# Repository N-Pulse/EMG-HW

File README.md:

# EMG-HW

This repository contains all the PCB designs for the EMG bracelet as part of a project semester at EPFL.

This work is licensed under a <a rel="license" href="https://creativecommons.org/licenses/by/4.0/">Creative Commons Attribution 4.0 International License</a>.

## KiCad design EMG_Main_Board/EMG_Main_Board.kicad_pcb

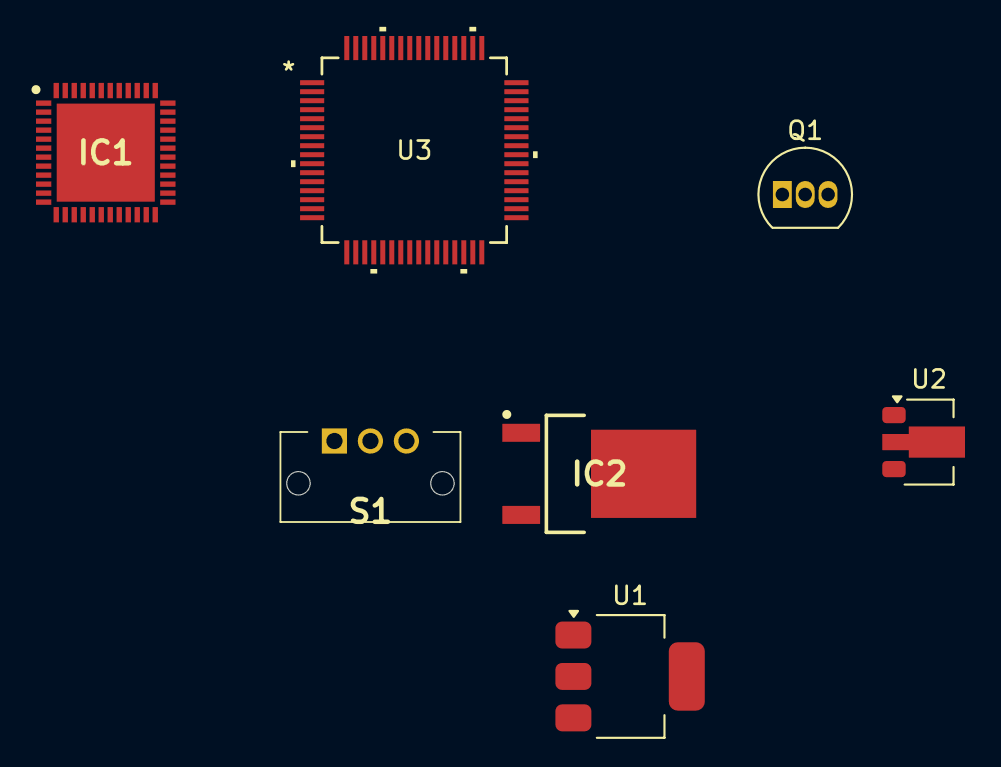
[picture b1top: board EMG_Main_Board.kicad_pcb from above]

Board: 2 copper layers, 7 parts (0 on the bottom side), 8 nets, no tracks yet.

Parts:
IC1: EFR32BG13P732F512GM48-D; QFN50P700X700X90-49N-D
IC2: LD1117DT18TR; TO228P972X240-3N
Q1: 2N3904; TO-92_Inline
S1: SC12P-AQR; SC12PAQR
U1: LD1117S33TR_SOT223; SOT-223-3_TabPin2
U2: NDP6802SF-33; SOT-89-3
U3: STM32G0B1RET6; LQFP_0B1RET6_STM

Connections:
GND: IC1.49 (VSS), IC2.1 (GND), Q1.1 (E), U1.1 (GND), U3.9 (VSS/VSSA)
unnamed: IC1.39 (VREGVDD), IC2.3 (VIN), S1.C1 (C1_NO), U3.8 (VDD/VDDA)
unnamed: Q1.3 (C), U2.2 (GND)
unnamed: S1.B1 (B1_COM), U1.2 (VO)
SPI_MISO: IC1.25 (PA0), U3.60 (PB6)
SPI_MOSI: IC1.26 (PA1), U3.61 (PB7)
SPI_NSS: IC1.28 (PA3), U3.63 (PB9)
SPI_SCK: IC1.27 (PA2), U3.62 (PB8)

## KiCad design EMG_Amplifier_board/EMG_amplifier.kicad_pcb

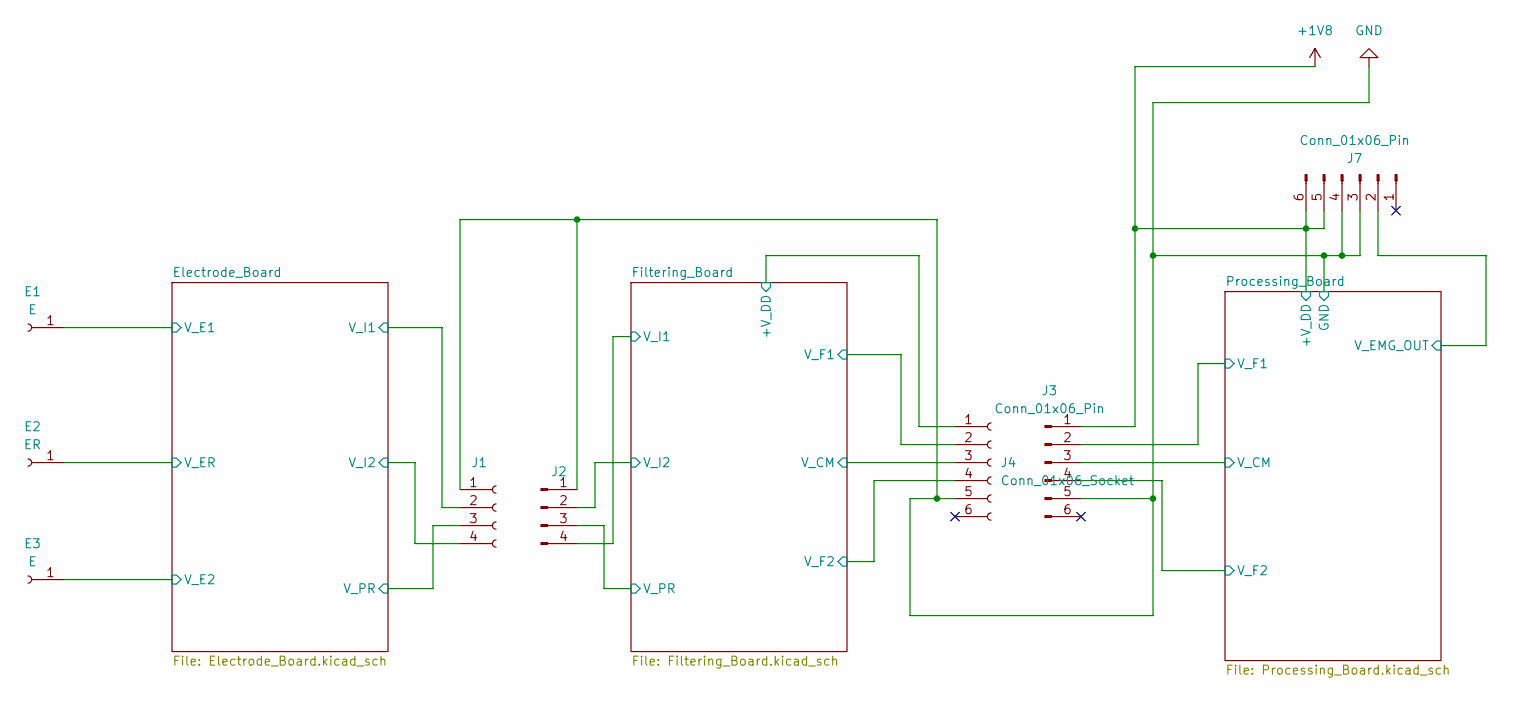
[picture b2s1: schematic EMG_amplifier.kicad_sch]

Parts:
E1, E3: E; Electrode_Shape
E2: ER; Electrode_Shape
J1: Conn_01x04_Socket; PinSocket_2x02_P2.54mm_Vertical
J2: Conn_01x04_Pin; PinHeader_2x02_P2.54mm_Vertical
J3, J7: Conn_01x06_Pin; PinHeader_2x03_P2.54mm_Vertical
J4: Conn_01x06_Socket; PinSocket_2x03_P2.54mm_Vertical

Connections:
+1V8: J3.1, J7.5, J7.6; also elsewhere on the board
/Electrode_Board/V_E1: E1.1; also elsewhere on the board
/Electrode_Board/V_E2: E3.1; also elsewhere on the board
/Electrode_Board/V_ER: E2.1; also elsewhere on the board
/Electrode_Board/V_I1: J1.2; also elsewhere on the board
/Electrode_Board/V_I2: J1.4; also elsewhere on the board
/Electrode_Board/V_PR: J1.3; also elsewhere on the board
/Filtering_Board/+V_DD: J4.1; also elsewhere on the board
/Filtering_Board/V_CM: J4.3; also elsewhere on the board
/Filtering_Board/V_F1: J4.2; also elsewhere on the board
/Filtering_Board/V_F2: J4.4; also elsewhere on the board
/Filtering_Board/V_I1: J2.4; also elsewhere on the board
/Filtering_Board/V_I2: J2.2; also elsewhere on the board
/Filtering_Board/V_PR: J2.3; also elsewhere on the board
/Processing_Board/V_CM: J3.3; also elsewhere on the board
/Processing_Board/V_EMG_OUT: J7.2; also elsewhere on the board
/Processing_Board/V_F1: J3.2; also elsewhere on the board
/Processing_Board/V_F2: J3.4; also elsewhere on the board
GND: J1.1, J2.1, J3.5, J4.5, J7.3, J7.4; also elsewhere on the board

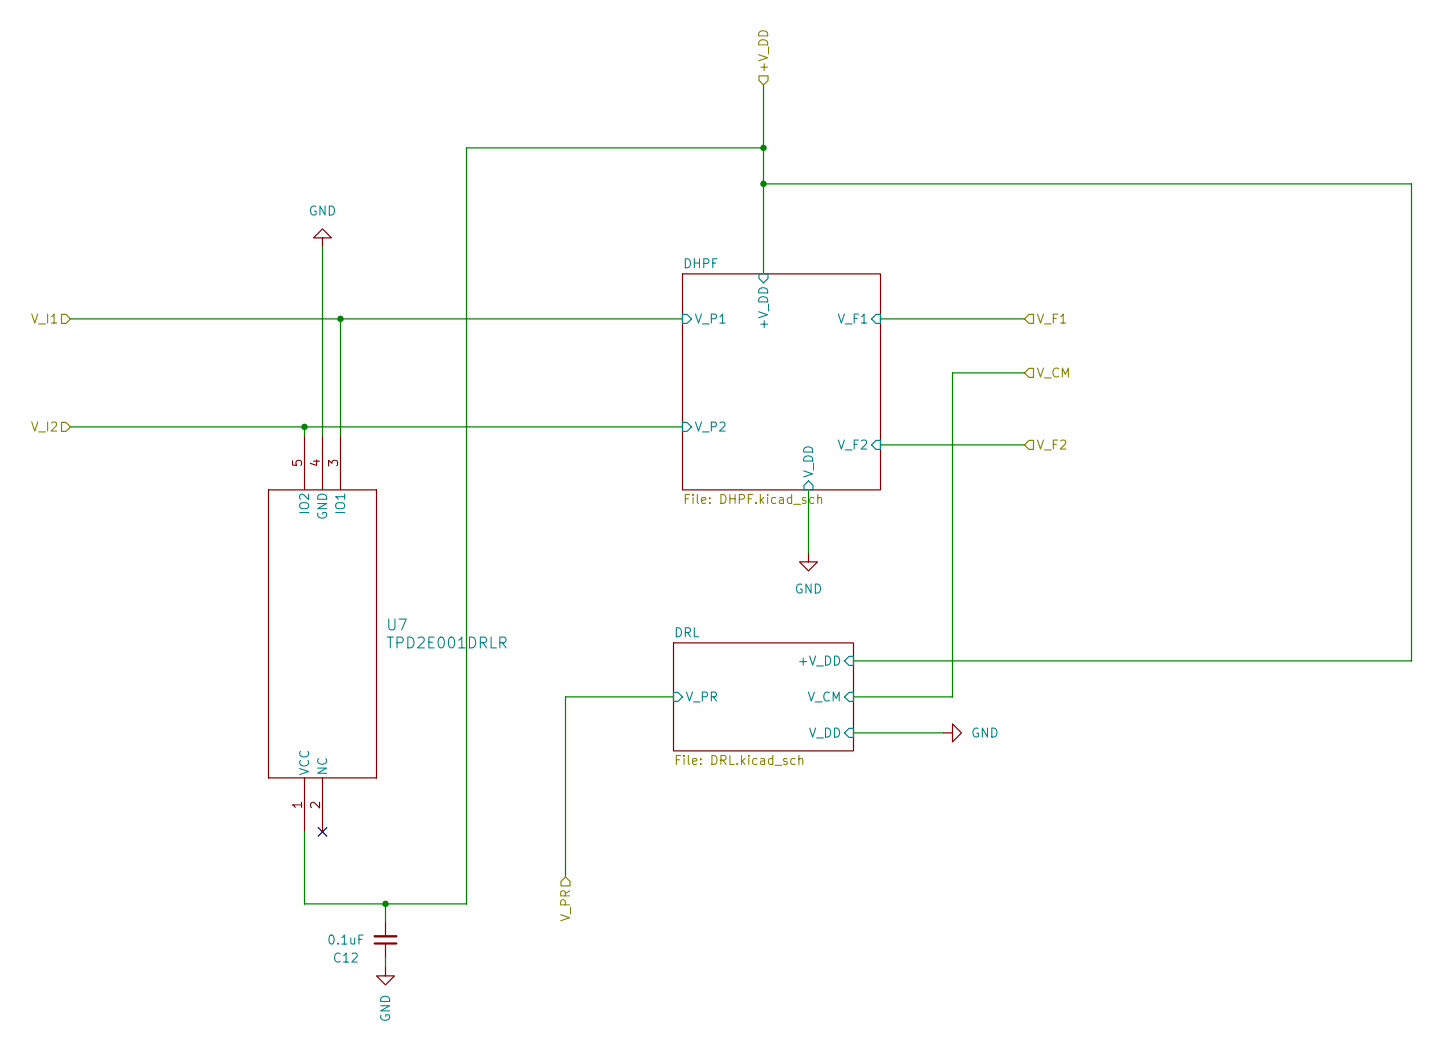
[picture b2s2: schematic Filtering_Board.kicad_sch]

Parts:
C12: 0.1uF; C_0402_1005Metric
U7: TPD2E001DRLR; DRL5-L

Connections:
/Filtering_Board/+V_DD: C12.2, U7.1 (VCC); also elsewhere on the board
/Filtering_Board/V_I1: U7.3 (IO1); also elsewhere on the board
/Filtering_Board/V_I2: U7.5 (IO2); also elsewhere on the board
GND: C12.1, U7.4 (GND); also elsewhere on the board

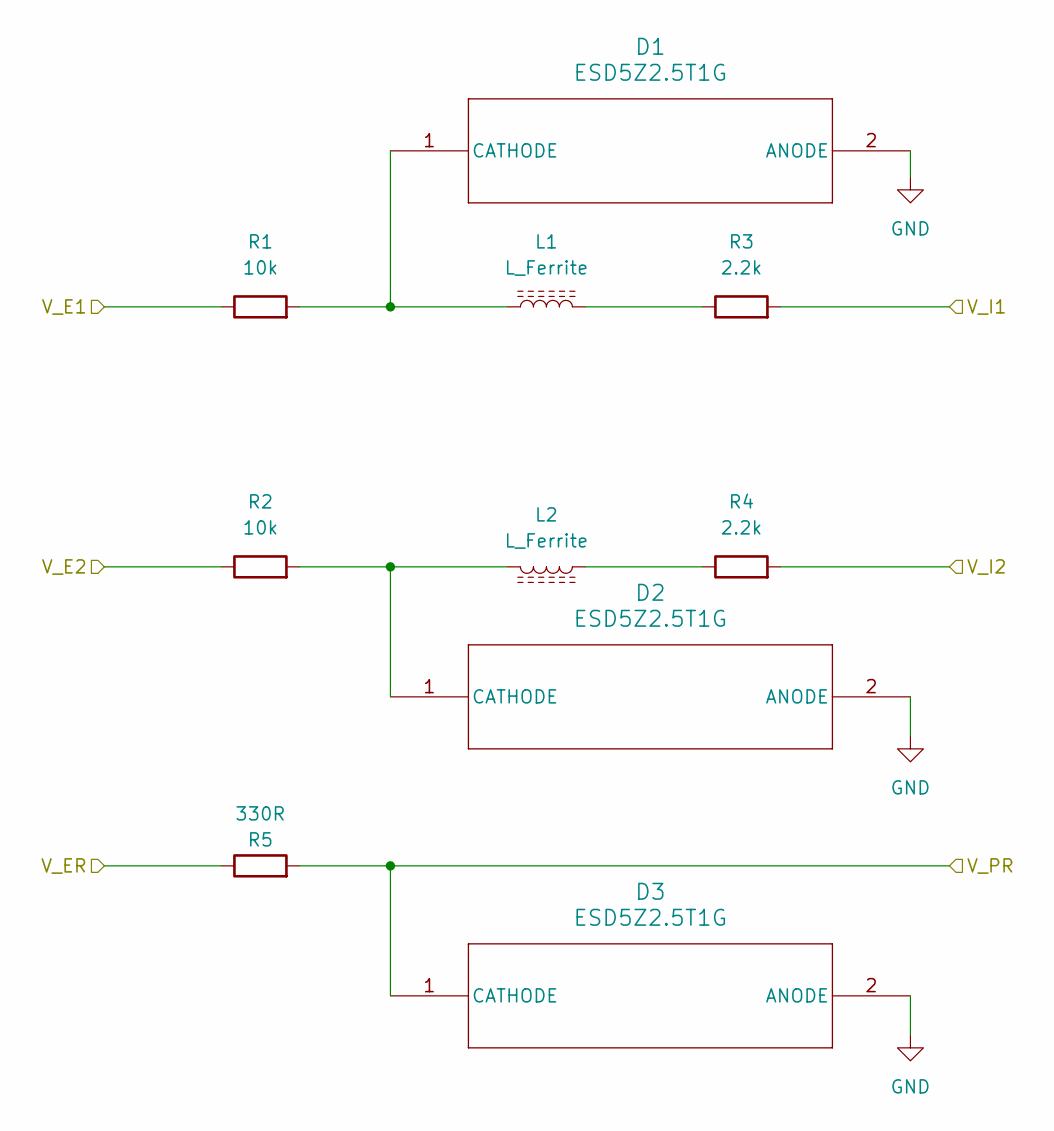
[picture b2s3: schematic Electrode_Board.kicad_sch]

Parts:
D1, D2, D3: ESD5Z2.5T1G; SOD-523_0P9X1P3_ONS
L1, L2: L_Ferrite; IND_BLM15_1P05X0P55X0P55_MUR
R1, R2: 10k; R_0402_1005Metric
R3, R4: 2.2k; R_0402_1005Metric
R5: 330R; R_0402_1005Metric

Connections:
/Electrode_Board/V_E1: R1.1; also elsewhere on the board
/Electrode_Board/V_E2: R2.1; also elsewhere on the board
/Electrode_Board/V_ER: R5.1; also elsewhere on the board
/Electrode_Board/V_I1: R3.2; also elsewhere on the board
/Electrode_Board/V_I2: R4.2; also elsewhere on the board
/Electrode_Board/V_PR: D3.1 (CATHODE), R5.2; also elsewhere on the board
GND: D1.2 (ANODE), D2.2 (ANODE), D3.2 (ANODE); also elsewhere on the board
unnamed: D1.1 (CATHODE), L1.1, R1.2
unnamed: D2.1 (CATHODE), L2.2, R2.2
unnamed: L1.2, R3.1
unnamed: L2.1, R4.1

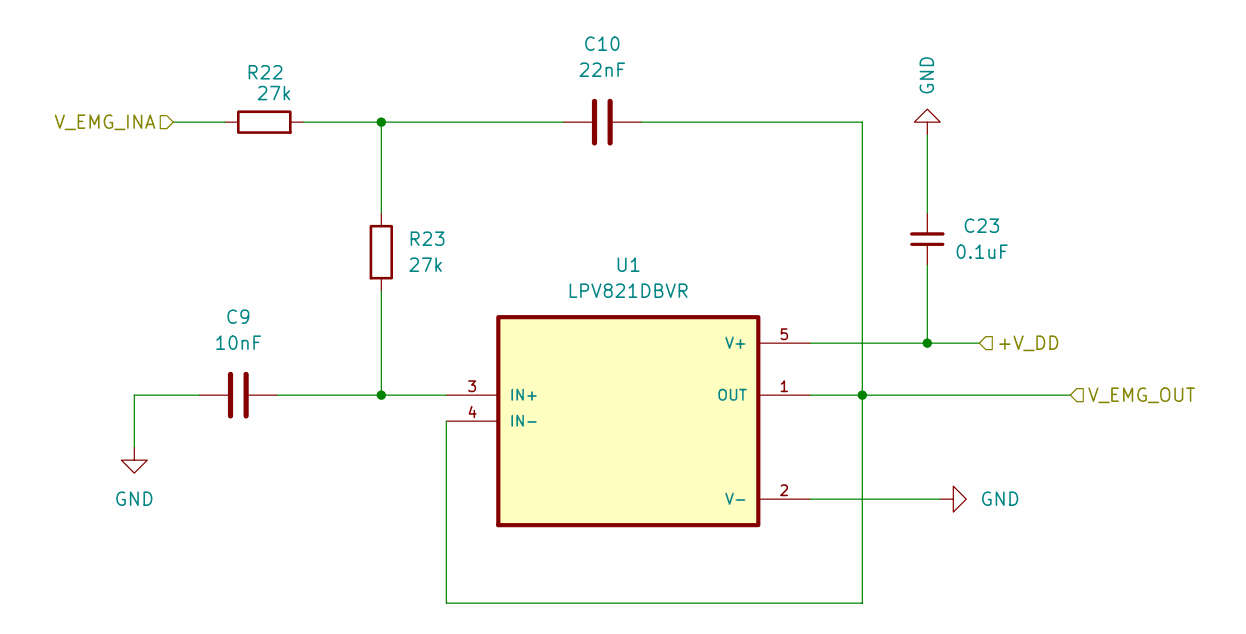
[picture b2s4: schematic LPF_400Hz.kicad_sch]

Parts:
C9: 10nF; C_0402_1005Metric
C10: 22nF; C_0805_2012Metric
C23: 0.1uF; C_0402_1005Metric
R22, R23: 27k; R_0402_1005Metric
U1: LPV821DBVR; SOT95P280X145-5N

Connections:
+1V8: C23.1, U1.5 (V+); also elsewhere on the board
/Processing_Board/LPF_400Hz/V_EMG_INA: R22.1; also elsewhere on the board
/Processing_Board/V_EMG_OUT: C10.2, U1.1 (OUT), U1.4 (IN-); also elsewhere on the board
GND: C9.1, C23.2, U1.2 (V-); also elsewhere on the board
unnamed: C10.1, R22.2, R23.1
unnamed: C9.2, R23.2, U1.3 (IN+)

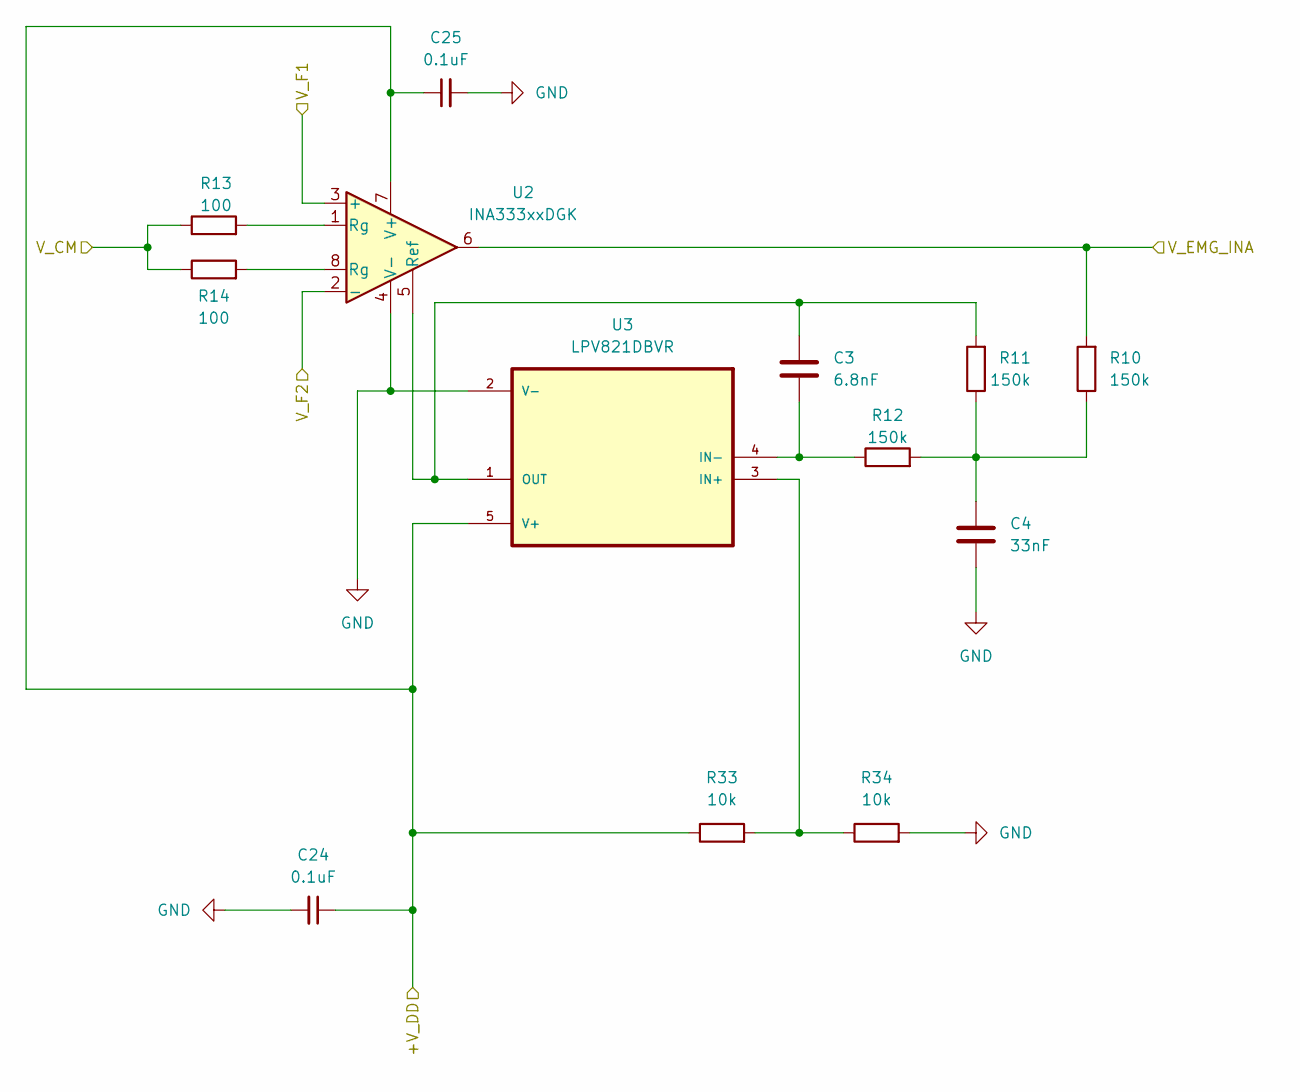
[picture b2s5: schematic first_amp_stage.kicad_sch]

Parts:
C3: 6.8nF; C_0603_1608Metric
C4: 33nF; C_0805_2012Metric
C24, C25: 0.1uF; C_0402_1005Metric
R10, R11, R12: 150k; R_0402_1005Metric
R13, R14: 100; R_0402_1005Metric
R33, R34: 10k; R_0402_1005Metric
U2: INA333xxDGK; VSSOP-8_3x3mm_P0.65mm
U3: LPV821DBVR; SOT95P280X145-5N

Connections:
+1V8: C24.1, C25.1, R33.1, U2.7 (V+), U3.5 (V+); also elsewhere on the board
/Processing_Board/LPF_400Hz/V_EMG_INA: R10.2, U2.6; also elsewhere on the board
/Processing_Board/V_CM: R13.1, R14.1; also elsewhere on the board
/Processing_Board/V_F1: U2.3 (+); also elsewhere on the board
/Processing_Board/V_F2: U2.2 (-); also elsewhere on the board
GND: C4.2, C24.2, C25.2, R34.2, U2.4 (V-), U3.2 (V-); also elsewhere on the board
unnamed: C4.1, R10.1, R11.1, R12.2
unnamed: R13.2, U2.1 (Rg)
unnamed: R14.2, U2.8 (Rg)
unnamed: C3.1, R11.2, U2.5 (Ref), U3.1 (OUT)
unnamed: R33.2, R34.1, U3.3 (IN+)
unnamed: C3.2, R12.1, U3.4 (IN-)

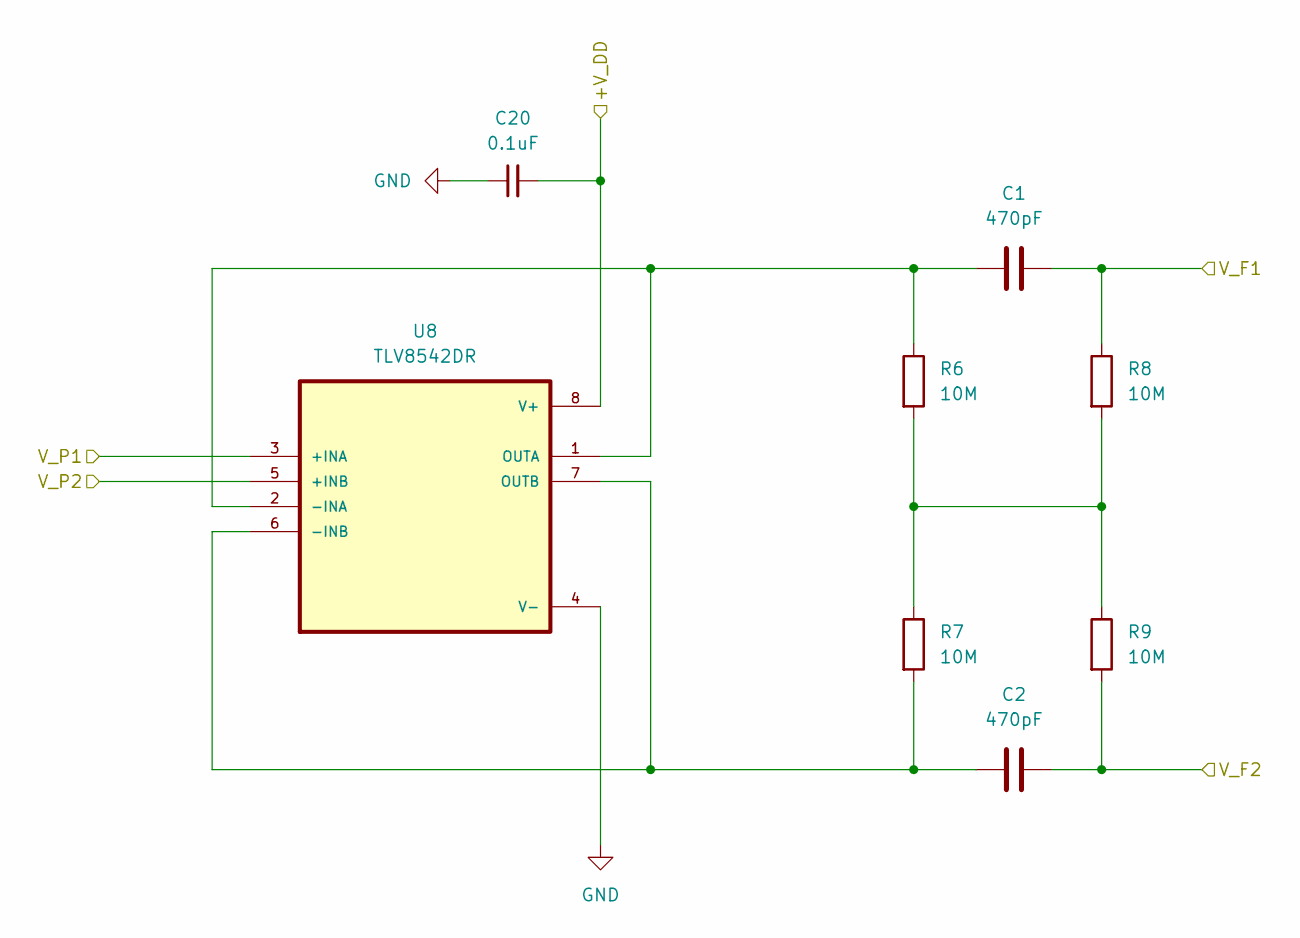
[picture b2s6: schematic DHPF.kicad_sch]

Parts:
C1, C2: 470pF; C_0603_1608Metric
C20: 0.1uF; C_0402_1005Metric
R6, R7, R8, R9: 10M; R_0402_1005Metric
U8: TLV8542DR; SOIC127P599X175-8N

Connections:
/Filtering_Board/+V_DD: C20.2, U8.8 (V+); also elsewhere on the board
/Filtering_Board/V_F1: C1.2, R8.1; also elsewhere on the board
/Filtering_Board/V_F2: C2.2, R9.2; also elsewhere on the board
/Filtering_Board/V_I1: U8.3 (+INA); also elsewhere on the board
/Filtering_Board/V_I2: U8.5 (+INB); also elsewhere on the board
GND: C20.1, U8.4 (V-); also elsewhere on the board
unnamed: R6.2, R7.1, R8.2, R9.1
unnamed: C1.1, R6.1, U8.1 (OUTA), U8.2 (-INA)
unnamed: C2.1, R7.2, U8.6 (-INB), U8.7 (OUTB)

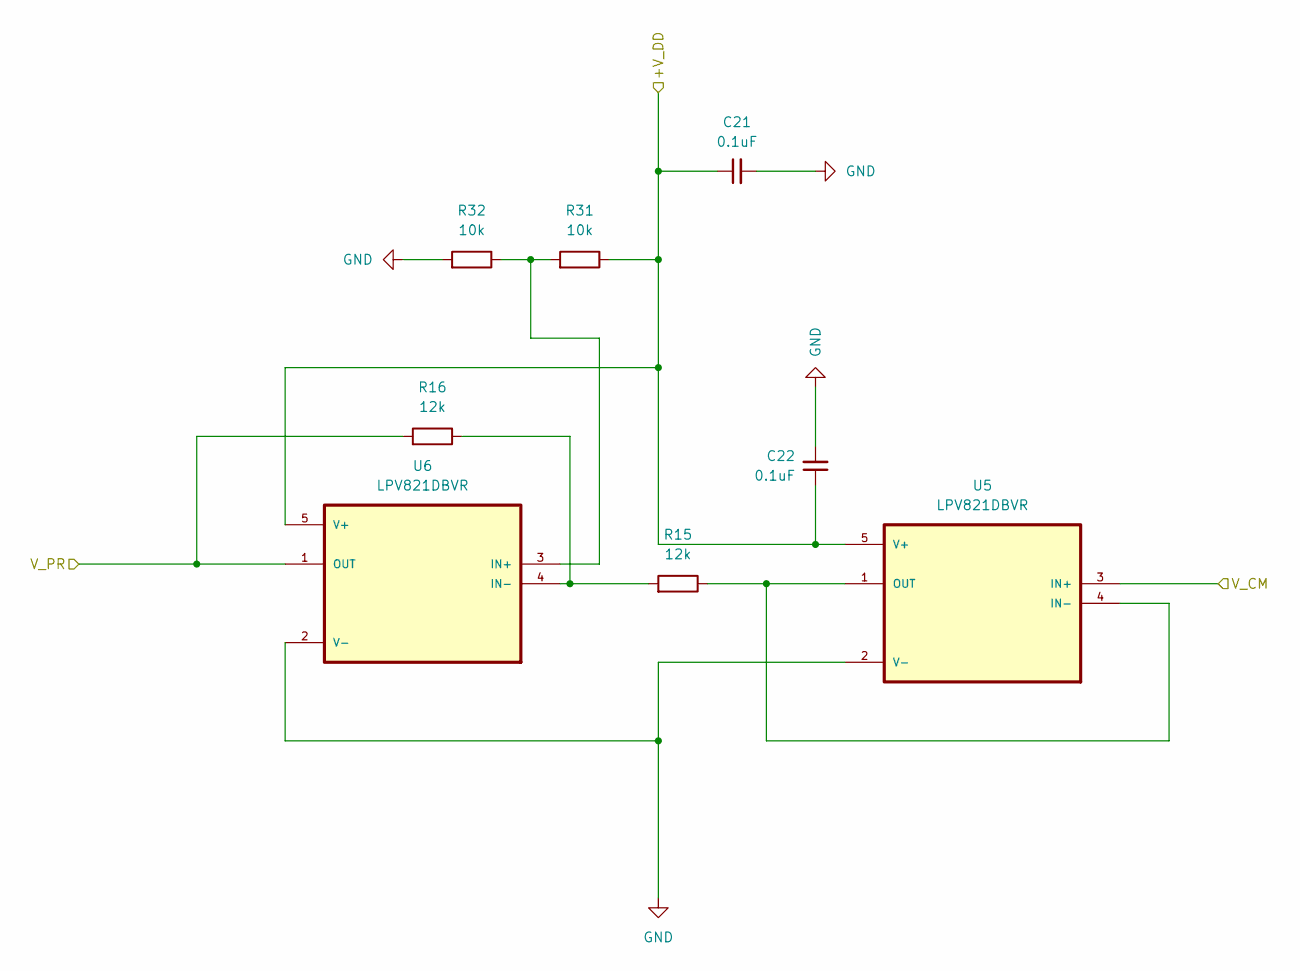
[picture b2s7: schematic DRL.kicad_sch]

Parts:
C21, C22: 0.1uF; C_0402_1005Metric
R15, R16: 12k; R_0402_1005Metric
R31, R32: 10k; R_0402_1005Metric
U5, U6: LPV821DBVR; SOT-23-5

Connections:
/Filtering_Board/+V_DD: C21.1, C22.1, R31.1, U5.5 (V+), U6.5 (V+); also elsewhere on the board
/Filtering_Board/V_CM: U5.3 (IN+); also elsewhere on the board
/Filtering_Board/V_PR: R16.2, U6.1 (OUT); also elsewhere on the board
GND: C21.2, C22.2, R32.2, U5.2 (V-), U6.2 (V-); also elsewhere on the board
unnamed: R15.1, U5.1 (OUT), U5.4 (IN-)
unnamed: R31.2, R32.1, U6.3 (IN+)
unnamed: R15.2, R16.1, U6.4 (IN-)

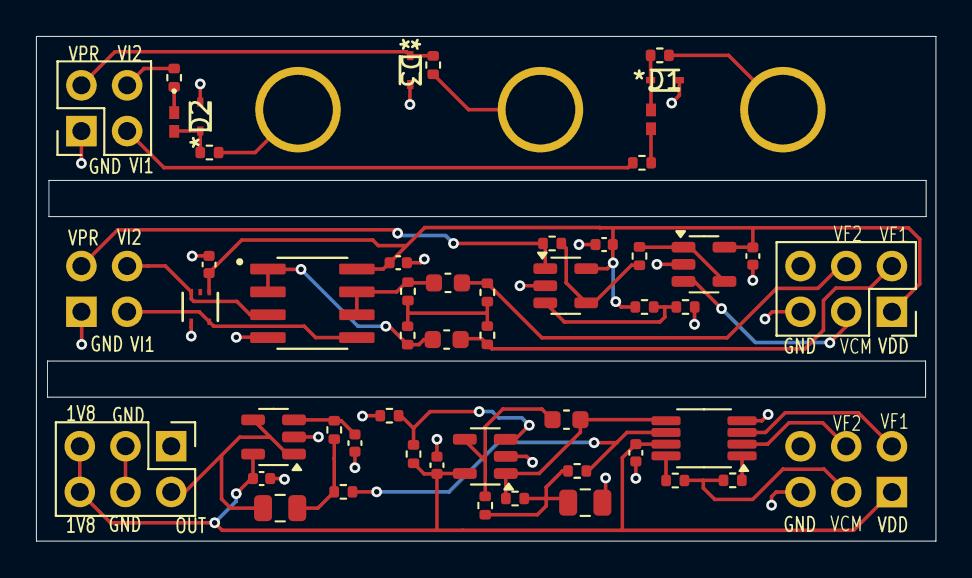
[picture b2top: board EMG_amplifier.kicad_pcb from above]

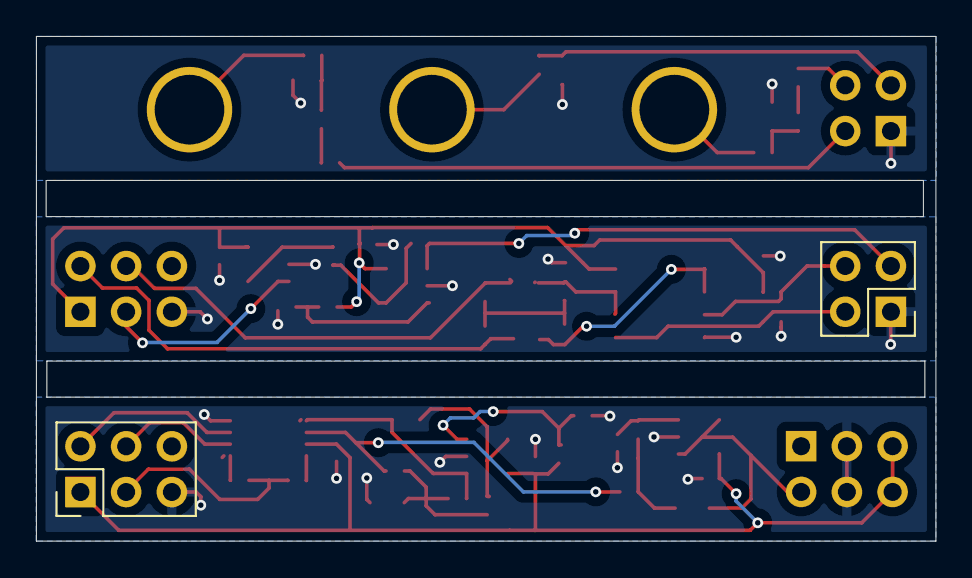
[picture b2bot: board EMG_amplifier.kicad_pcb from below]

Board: 4 copper layers, 50.0 x 28.0 mm, 55 parts (2 on the bottom side), 38 nets.

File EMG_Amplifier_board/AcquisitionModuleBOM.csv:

"Id";"Designator";"Footprint";"Quantity";"Designation";"Supplier and ref";
1;"J4";"PinSocket_2x03_P2.54mm_Vertical";1;"Conn_01x06_Socket";;;
2;"R23,R22";"R_0402_1005Metric";2;"27k";;;
3;"J7,J3";"PinHeader_2x03_P2.54mm_Vertical";2;"Conn_01x06_Pin";;;
4;"R14,R13";"R_0402_1005Metric";2;"100";;;
5;"C2,C1";"C_0603_1608Metric";2;"470pF";;;
6;"D3,D2,D1";"SOD-523_0P9X1P3_ONS";3;"ESD5Z2.5T1G";;;
7;"C12,C24,C21,C22,C23,C20,C25";"C_0402_1005Metric";7;"0.1uF";;;
8;"U3,U5,U6,U1";"SOT95P280X145-5N";4;"LPV821DBVR";;;
9;"R10,R11,R12";"R_0402_1005Metric";3;"150k";;;
10;"U7";"DRL5-L";1;"TPD2E001DRLR";;;
11;"R34,R31,R32,R33,R1,R2";"R_0402_1005Metric";6;"10k";;;
12;"R9,R8,R6,R7";"R_0402_1005Metric";4;"10M";;;
13;"E3,E1";"Electrode_Shape";2;"E";;;
14;"R3,R4";"R_0402_1005Metric";2;"2.2k";;;
15;"R16,R15";"R_0402_1005Metric";2;"12k";;;
16;"C3";"C_0603_1608Metric";1;"6.8nF";;;
17;"U2";"VSSOP-8_3x3mm_P0.65mm";1;"INA333xxDGK";;;
18;"C10";"C_0805_2012Metric";1;"22nF";;;
19;"E2";"Electrode_Shape";1;"ER";;;
20;"U8";"SOIC127P599X175-8N";1;"TLV8542DR";;;
21;"C9";"C_0402_1005Metric";1;"10nF";;;
22;"C4";"C_0805_2012Metric";1;"33nF";;;
23;"L2,L1";"IND_BLM15_1P05X0P55X0P55_MUR";2;"L_Ferrite";;;
24;"R5";"R_0402_1005Metric";1;"330R";;;
25;"J1";"PinSocket_2x02_P2.54mm_Vertical";1;"Conn_01x04_Socket";;;
26;"J2";"PinHeader_2x02_P2.54mm_Vertical";1;"Conn_01x04_Pin";;;

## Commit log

2024-09-29 fEMG schematics in progress
2024-10-01 add footprints
2024-10-03 acomponents choice
2024-10-07 update the schematic with shared grounds and pin connectors
2024-10-14 pcb design v1
2024-10-14 use one C10 capacitor instead of both C9 and C10
2024-10-14 add vias for electrodes
2024-10-14 minor link addition
2024-10-23 before working on one-sided design
2024-10-24 place all components on one side
2024-10-28 first revision
2024-10-28 remove multiple warnings
2024-10-28 minor gnd trace change
2024-10-28 add edge cuts
2024-10-28 update EMG.zip file
2024-10-28 increase the width of the electrode vias' annular ring
2024-10-30 add a sentence to the README
2024-11-12 center the pin connectors
2024-11-12 board V1
2024-11-18 remove panel design
2024-11-18 add grounding vias
2024-11-20 connect TLV8542 to VDD
2024-11-20 lock electrode pads and pin headers
2024-11-21 add capacitor to ESD
2024-11-22 correct the 400Hz LPF schematic and InAmp trace routing
2024-11-22 aesthetics
2024-11-23 retrace routes that passed under resistances
2024-11-23 connect InAmp LPV821 to GND
2024-11-23 update R and C refs to correspond to paper
2024-11-23 replace 2012 capacitors with 1005
2024-11-23 minor changes
2024-11-23 update ferrite beads' and zener diodes' footprints
2024-11-23 modify layout to add space around electrodes
2024-11-25 minor spacing changes
2024-11-25 switch LPV821 footprint package to SOT-23-5
2024-12-05 add MCU and BLE to main board schematic
2025-01-05 add buck converter 3v3 to 1v8, start new two-board sigacq project
2025-01-06 switch to LDO for 1v8 and add LDO for cste 3.3V pwr supply
2025-01-06 add 38.4 and 48MHz crystals for BLE and MCU, resp.
2025-01-06 add ON/OFF slide switch and RST button to sch
2025-01-06 replace slide switch
2025-03-12 add license
2025-03-16 remove abandonned main board project
